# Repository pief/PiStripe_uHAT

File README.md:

# PiStripe uHAT

## Background

Surely I'm not the only one having both a Raspberry Pi and an LED stripe flying around. In my case it was a "dumb", analogue 12V RGB LED stripe, meaning an LED strip without individually addressable LEDs - instead you generate different colors on the entire LED stripe by using pulse width modulation (PWM) on the R, G and B lines.

Interestingly, while there are plenty of tutorials on connecting such an LED stripe to the Raspberry Pi using transistors I wasn't able to find a ready-to-use HAT doing this. There are plenty of HATs driving LEDs directly mounted on the HAT (e.g. [Pimoroni's Ubercorn](https://shop.pimoroni.com/products/ubercorn) and [Unicorn](https://shop.pimoroni.com/products/unicorn-hat) HATs) and
there is [ManiacalLabs' PiPixel HAT](https://www.tindie.com/products/ManiacalLabs/pipixel-raspberry-pi-led-strip-hat/) but that one drives "digital" WS2812-based LED strips, not dumb ones such as mine. Knight of Pi simply [soldered the transistors on Adafruit's ProtoHAT](http://www.knight-of-pi.org/color-mixer-control-a-rgb-led-strip-with-the-raspberry-pi-and-the-n-channel-mosfet-irlb8721/)
but that seemed to me a bit too hackish for permanent use.

The closest existing solution is the [ANAVI Light pHAT](https://www.crowdsupply.com/anavi-technology/light-phat). It is designed for 12V RGB LED strips such as mine, however there were some points I didn't like. For instance, it uses a quite big screw terminal
where I'd prefer a more compact pin header that matches the existing LED strip connector. But most of all, I don't like having to use two power supplies, one with 12V for the LED strip and still one with 5V for the Raspberry Pi. Unfortunately, with the ANAVI pHAT, it was decided to not implement the back powering option, i.e. integrating a switching regulator to convert 12V to 5V and supply these to the Raspberry Pi via the GPIO pins. Instead the PCB space was used for various options for all kinds of sensors,
something I don't really need.

So I thought, inspite of being not literate at electronics enough I'd build something myself and take the best parts and features of existing solutions and combine them into a HAT of my own. After all, that's what open hardware is all about!

And with great success: the PiStripe uHAT has now been built and tested successfully!

## Features

The PiStripe uHAT is a board of the size of the Raspberry Pi Zero, thus a uHAT (not a HAT) as defined by the Raspberry Foundation. It can be attached on any Raspberry Pi with the 40 pin connector, not just the Pi Zero (W).

The uHAT features the following five functions:

- a 12V -> 5V buck converter based on Texas Instruments' [TPS54202](http://www.ti.com/lit/ds/symlink/tps54202.pdf) chip to implement "back powering" the Raspberry Pi via the GPIO pins, doing away with the need to use two power supplies (one 12V for the LED strip, one 5V for the Raspberry Pi).
- a "perfect" reverse current blocking diode schematic as described in the
  [Raspberry Foundation Add-On board / HAT design guide](https://github.com/raspberrypi/hats/blob/master/designguide.md) to prevent damage when accidentally connecting both 5V to the RPi via its MicroUSB connector and supplying power via my HAT does
  not cause damage.
- the actual LED strip driving
- the possibility to connect an external IR receiver such as a TSOP 34838 so you can use [LIRC](http://lirc.org/) to decode the signals sent by the LED strip's original remote control. External because the HAT is mounted on the Raspberry Pi which in turn will probably be hidden away in some corner whereas you will want to place the IR receiver at a place where it can actually "see" the remote control.
- an ID EEPROM so the board qualifies officially as a HAT as described in the [Raspberry Foundation Add-On board / HAT design guide](https://github.com/raspberrypi/hats/blob/master/designguide.md).

## Hardware

The PiStripe uHAT is not a ready-to-buy product. In fact it's not even a product as such. Instead, it's a do-it-yourself project. Consult the **Hardware** directory for the KiCad project files, including a parts list and the PCB ready for etching.

## Software

The PiStripe uHAT's ID EEPROM needs to be programmed once with the binary in the **Software/EEPROM** directory. The **Software** directory additionally contains some examples on how to use the PiStripe uHAT.

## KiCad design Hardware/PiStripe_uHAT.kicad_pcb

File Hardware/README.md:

# PiStripe uHAT

## Hardware

The current v0.7 revision of the PiStripe uHAT has been successfully built and tested with the following remarks nonwithstanding:
- the pullups R9, R11 and R13 are probably unnecessary if the ID EEPROM is changed to use the Raspberry Pi's internal pull-up resistors.
- I used a bit of a too small font size, so if you can't read everything, it's not your eyes...

### GPIOs used

The PiStripe uHAT uses the following GPIO pins:

|          GPIO pins           |    Pin name     |            Usage           | Exclusive |
| :--------------------------: | :-------------: | :------------------------: | :-------: |
|              1, 17           |      +3.3V      |   IR receiver, ID EEPROM   |    No     |
|              2, 4            |       +5V       | Back powering Raspberry Pi |    No     |
| 6, 9, 14, 20, 25, 30, 34, 39 |       GND       |           Ground           |    No     |
|               19             | GPIO10_SPI_MOSI |   LED color 1 (e.g. Red)   |    Yes    |
|               21             | GPIO09_SPI_MISO |  LED color 2 (e.g. Green)  |    Yes    |
|               22             |      GPIO25     |      IR receiver data      |    Yes    |
|               23             | GPIO11_SPI_CLK  |   LED color 3 (e.g. Blue)  |    Yes    |
|               27             |      ID_SD      |     ID EEPROM I2C Data     |    No     |
|               28             |      ID_SC      |     ID EEPROM I2C Clock    |    No     |

### Jumpers

There are two jumpers:

| Jumper |   Name   |                        Function                        |
| :----: | :------: | :----------------------------------------------------: |
|  JP1   | GPIO_PWR | Open: Raspberry Pi is powered over Micro USB connector |
|        | GPIO_PWR | Closed: Enable back powering the Raspberry Pi via GPIO |
|  JP2   |   WR_EN  |                   Open: Normal usage                   |
|        |   WR_EN  |           Closed: ID EEPROM can be programmed          |

Whether you leave JP1 open or closed depends on whether you want to use the "back powering" feature, thus requiring only the LED stripe's +12V power supply, or keep supplying the Raspberry Pi via its Micro USB connector. Even if you accidentally close JP1 and still connect power to the Pi's Micro USB connector, nothing should go wrong thanks to the "perfect" reverse current blocking diode.

JP2 should only be closed once to program the ID EEPROM (no instructions and software for this yet) and stay open afterwards to prevent accidental flashing.

### Design files

The board's schematic and PCB have been designed with [KiCad](http://www.kicad-pcb.org), a really powerful Open Source EDA solution and a worthy alternative to commercial products such as Eagle.

#### Schematic

Here's an image of the schematic:

As you can see, the schematic is clearly divided into different blocks that corrospond to the functions listed above, so comparisons with the original sources for the schematics (see [Credits](#credits)) should be rather easy.

#### PCB

Here are some images of the PCB:

Like the schematic, the PCB has guiding lines printed on top to isolate the different function blocks.

#### Parts list

Please consult the [CSV part list](Hardware/PiStripe_uHAT_Parts.csv) for details.

### Credits

I'm not really inventing something new here but merely combining existing stuff into something new, so I'm standing on the shoulders of giants and try to give appropriate credits here. A big "Thank you" to the following people:

- **Alain Pannetrat** posted the Texas Instruments' [TPS54202](http://www.ti.com/lit/ds/symlink/tps54202.pdf)-based schematic and PCB for [Adding a DC power jack to the Raspberry Pi](https://www.omzlo.com/articles/adding-a-dc-power-jack-to-the-raspberry-pi-v2) on his omzlo.com blog. He did not explicitly specify a license, so I'll assume CC-BY-SA.
- **The Raspberry Foundation** published the circuit for the "perfect" reverse current blocking diode in their [Add-On board / HAT design guide](https://github.com/raspberrypi/hats/blob/master/designguide.md) (see the section "Back Powering the Pi via the GPIO Header" there and the [ZVD circuit schematic](https://github.com/raspberrypi/hats/blob/master/zvd-circuit.png).
- **Leon Anavi** published the schematic and PCB for his [ANAVI Light pHAT](https://www.crowdsupply.com/anavi-technology/light-phat) and his [ANAVI Infrared pHAT](https://www.crowdsupply.com/anavi-technology/infrared-phat) under the [CC-BY-SA 4.0](https://creativecommons.org/licenses/by-sa/4.0/) license. The LED driving circuit, the IR receiver circuit and the basic PCB design such as board dimensions, mounting holes etc. are based on his work. Note that for the IR receiver I use pin 22 (GPI25) instead of pin 12 (GPIO18) to be compatible with the [pHAT DAC](https://de.pinout.xyz/pinout/phat_dac).
- **Mike Lawrence** posted a [RPi_Zero_pHat_Template](https://github.com/mikelawrence/RPi_Zero_pHat_Template) from which I used symbols in ``Connector-ML.lib`` for the schematic. The template is licensed under the [MIT license](https://github.com/mikelawrence/RPi_Zero_pHat_Template/blob/master/LICENSE).
- **Digikey** provides a [KiCAD library](https://github.com/digikey/digikey-kicad-library) from which I used symbols in ``dk_Transistors-FETs-MOSFETs-Single.lib`` for the schematic. The library is licensed under the [CC-BY-SA 4.0](https://github.com/digikey/digikey-kicad-library/blob/master/LICENSE.md) license.
- **L. Bernstone** posted the schematic and design for a [3V3 DC/DC power supply layout using TPS54202](https://github.com/lbernstone/TPS54202/) from which I used symbols in ``tps54202.lib`` for the schematic.
- **Tinkerforge** provides [KiCAD libraries](https://github.com/Tinkerforge/kicad-libraries) from which I used symbols in ``DMMT5401.lib`` for the schematic. They are licensed under the [CERN Open Hardware License v1.1](https://github.com/Tinkerforge/kicad-libraries/blob/master/LICENSE.txt).
- **Philipp "Virtex7" Hörauf** provides a [Philipps Kicad Bauteile collection](https://github.com/Virtex7/PhilippsKicadBauteile/) from which I used the footprint ``SRU1048.kicad_mod`` in the PCB design. Since it didn't provide a 3D model, I modified it to use the one from the following paragraph. Philipp did not explicitly specify a license, so I'll assume CC-BY-SA.
- **ACSE & CADIEEL** provide [CIAA Hardware repository](https://github.com/ciaa/Hardware) from which I used the 3D model ``SRU1048.wrl`` together with the footprint in the previous paragraph. They use [their own license](https://github.com/ciaa/Hardware/blob/master/LICENSE).

### LICENSE

The PiStripe uHAT PCB and its design files are licensed [CC-BY-SA](LICENSE).

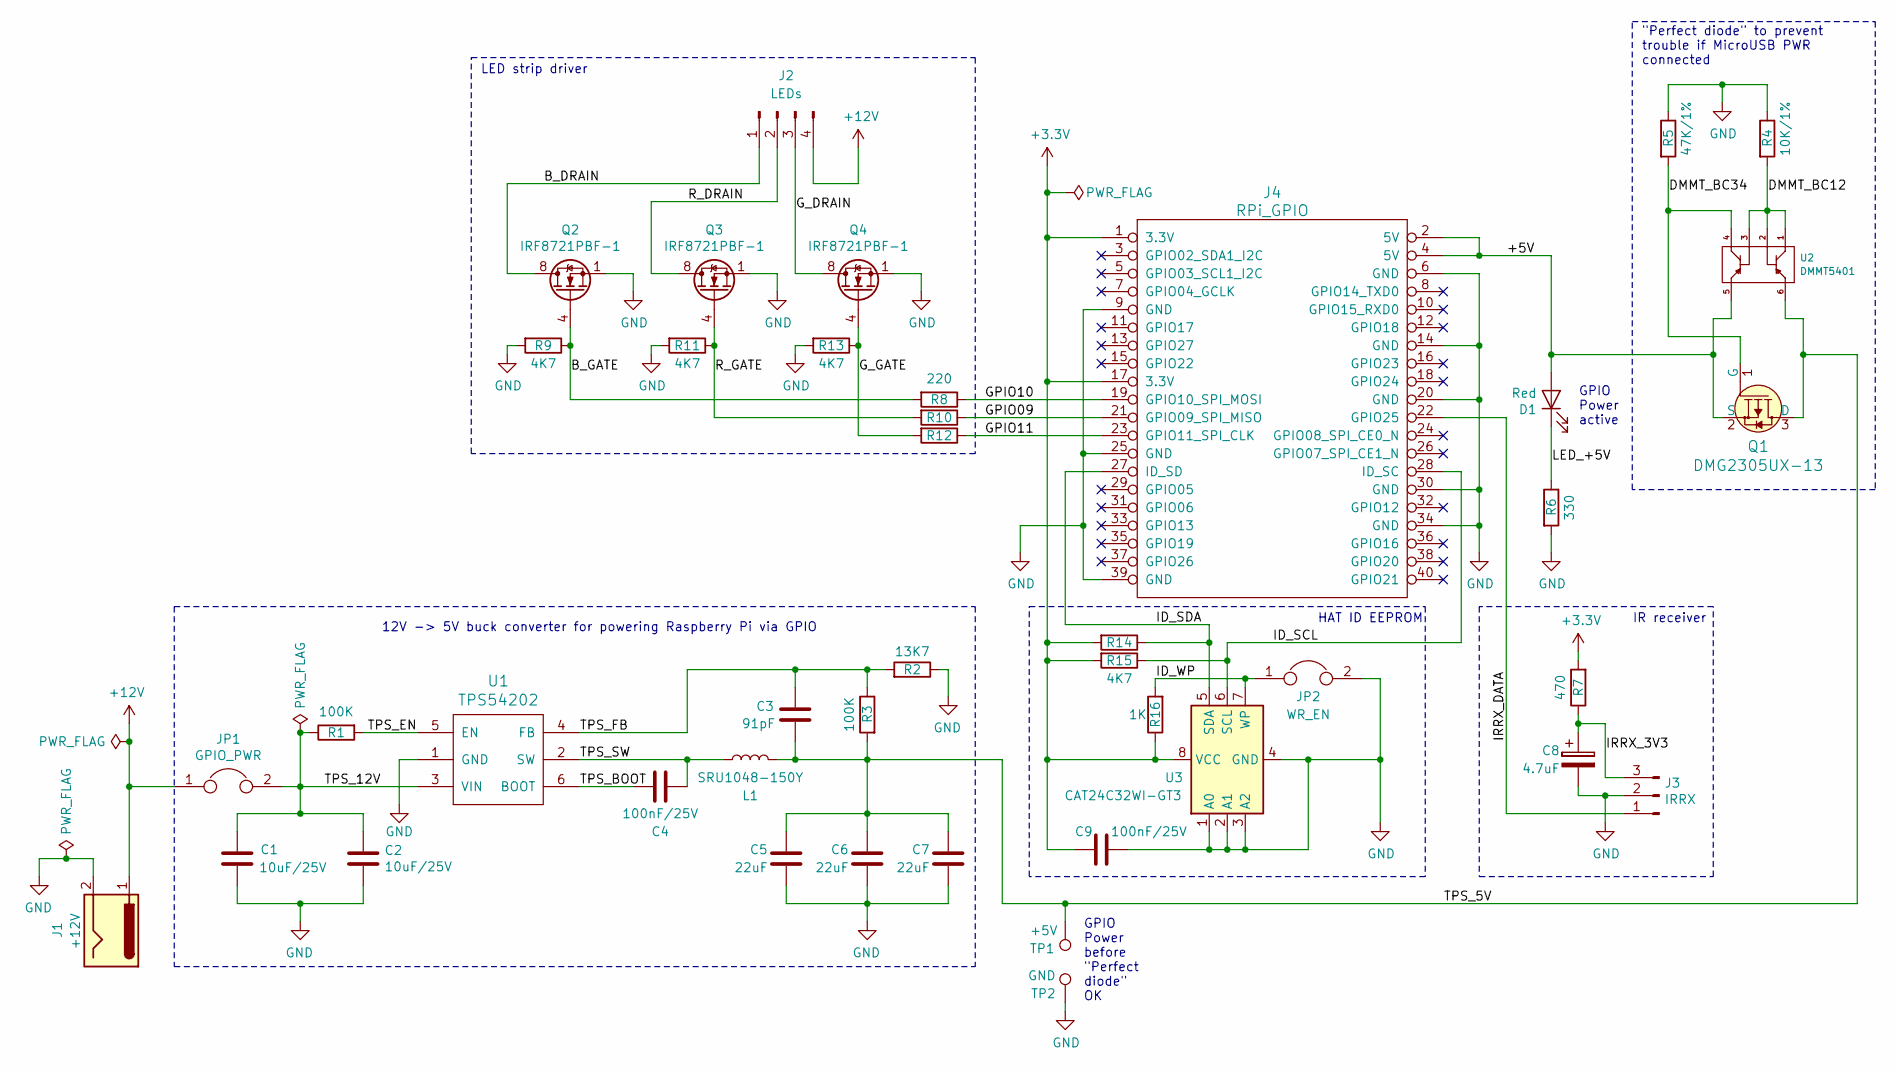
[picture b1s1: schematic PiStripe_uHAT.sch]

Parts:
C1, C2: 10uF/25V; C_0805_2012Metric_Pad1.15x1.40mm_HandSolder
C3: 91pF; C_0805_2012Metric_Pad1.15x1.40mm_HandSolder
C4, C9: 100nF/25V; C_0805_2012Metric_Pad1.15x1.40mm_HandSolder
C5, C6, C7: 22uF; C_0805_2012Metric_Pad1.15x1.40mm_HandSolder
C8: 4.7uF; CP_Elec_4x5.8
D1: Red; D_0805_2012Metric
J1: +12V; BarrelJack_CUI_PJ-063AH_Horizontal
J2: LEDs; PinSocket_1x04_P2.54mm_Horizontal
J3: IRRX; PinHeader_1x03_P2.54mm_Horizontal_Mirrored
J4: RPi_GPIO; PinSocket_2x20_P2.54mm_Vertical
JP1: GPIO_PWR; PinHeader_1x02_P2.54mm_Vertical
JP2: WR_EN; PinHeader_1x02_P1.27mm_Vertical
L1: SRU1048-150Y; SRU1048
Q1: DMG2305UX-13; SOT-23; MPN DMG2305UX-13; Digi-Key_PN DMG2305UX-13DICT-ND
Q2, Q3, Q4: IRF8721PBF-1; SOIC-8_3.9x4.9mm_P1.27mm
R1, R3: 100K; R_0805_2012Metric_Pad1.15x1.40mm_HandSolder
R2: 13K7; R_0805_2012Metric_Pad1.15x1.40mm_HandSolder
R4: 10K/1%; R_0805_2012Metric_Pad1.15x1.40mm_HandSolder
R5: 47K/1%; R_0805_2012Metric_Pad1.15x1.40mm_HandSolder
R6: 330; R_0805_2012Metric_Pad1.15x1.40mm_HandSolder
R7: 470; R_0805_2012Metric_Pad1.15x1.40mm_HandSolder
R8, R10, R12: 220; R_0805_2012Metric_Pad1.15x1.40mm_HandSolder
R9, R11, R13, R14, R15: 4K7; R_0805_2012Metric_Pad1.15x1.40mm_HandSolder
R16: 1K; R_0805_2012Metric_Pad1.15x1.40mm_HandSolder
TP1: +5V; TestPoint_Pad_D1.0mm
TP2: GND; TestPoint_Pad_D1.0mm
U1: TPS54202; SOT-23-6_Handsoldering
U2: DMMT5401; SOT-23-6_Handsoldering
U3: CAT24C32WI-GT3; SOIC-8_3.9x4.9mm_P1.27mm

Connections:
+3V3: C9.2, J4.1 (3.3V), J4.17 (3.3V), R7.2, R14.2, R15.2, R16.1, U3.8 (VCC)
+12V: J1.1, J2.4, JP1.1
/+5V: D1.2 (A), J4.2 (5V), J4.4 (5V), Q1.2 (S), U2.5
/B_DRAIN: J2.1, Q2.5 (D), Q2.6 (D), Q2.7 (D), Q2.8 (D)
/B_GATE: Q2.4 (G), R8.2, R9.1
/DMMT_BC12: R4.2, U2.1, U2.2, U2.3
/DMMT_BC34: Q1.1 (G), R5.2, U2.4
/GPIO09: J4.21 (GPIO09_SPI_MISO), R10.1
/GPIO10: J4.19 (GPIO10_SPI_MOSI), R8.1
/GPIO11: J4.23 (GPIO11_SPI_CLK), R12.1
/G_DRAIN: J2.3, Q4.5 (D), Q4.6 (D), Q4.7 (D), Q4.8 (D)
/G_GATE: Q4.4 (G), R12.2, R13.1
/ID_SCL: J4.28 (ID_SC), R15.1, U3.6 (SCL)
/ID_SDA: J4.27 (ID_SD), R14.1, U3.5 (SDA)
/ID_WP: JP2.1, R16.2, U3.7 (WP)
/IRRX_3V3: C8.1, J3.3, R7.1
/IRRX_DATA: J3.1, J4.22 (GPIO25)
/LED_+5V: D1.1 (K), R6.1
/R_DRAIN: J2.2, Q3.5 (D), Q3.6 (D), Q3.7 (D), Q3.8 (D)
/R_GATE: Q3.4 (G), R10.2, R11.1
/TPS_5V: C3.2, C5.1, C6.1, C7.1, L1.1, Q1.3 (D), R3.2, TP1.1, U2.6
/TPS_12V: C1.1, C2.1, JP1.2, R1.1, U1.3 (VIN)
/TPS_BOOT: C4.1, U1.6 (BOOT)
/TPS_EN: R1.2, U1.5 (EN)
/TPS_FB: C3.1, R2.2, R3.1, U1.4 (FB)
/TPS_SW: C4.2, L1.2, U1.2 (SW)
GND: C1.2, C2.2, C5.2, C6.2, C7.2, C8.2, C9.1, J1.2, J3.2, J4.6 (GND), J4.9 (GND), J4.14 (GND), J4.20 (GND), J4.25 (GND), J4.30 (GND), J4.34 (GND), J4.39 (GND), JP2.2, Q2.1 (S), Q2.2 (S), Q2.3 (S), Q3.1 (S), Q3.2 (S), Q3.3 (S), Q4.1 (S), Q4.2 (S), Q4.3 (S), R2.1, R4.1, R5.1, R6.2, R9.2, R11.2, R13.2, TP2.1, U1.1 (GND), U3.1 (A0), U3.2 (A1), U3.3 (A2), U3.4 (GND)

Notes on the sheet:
"Perfect diode" to prevent trouble if MicroUSB PWR connected
12V -> 5V buck converter for powering Raspberry Pi via GPIO
LED strip driver
IR receiver
HAT ID EEPROM
GPIO Power active
GPIO Power before "Perfect diode" OK

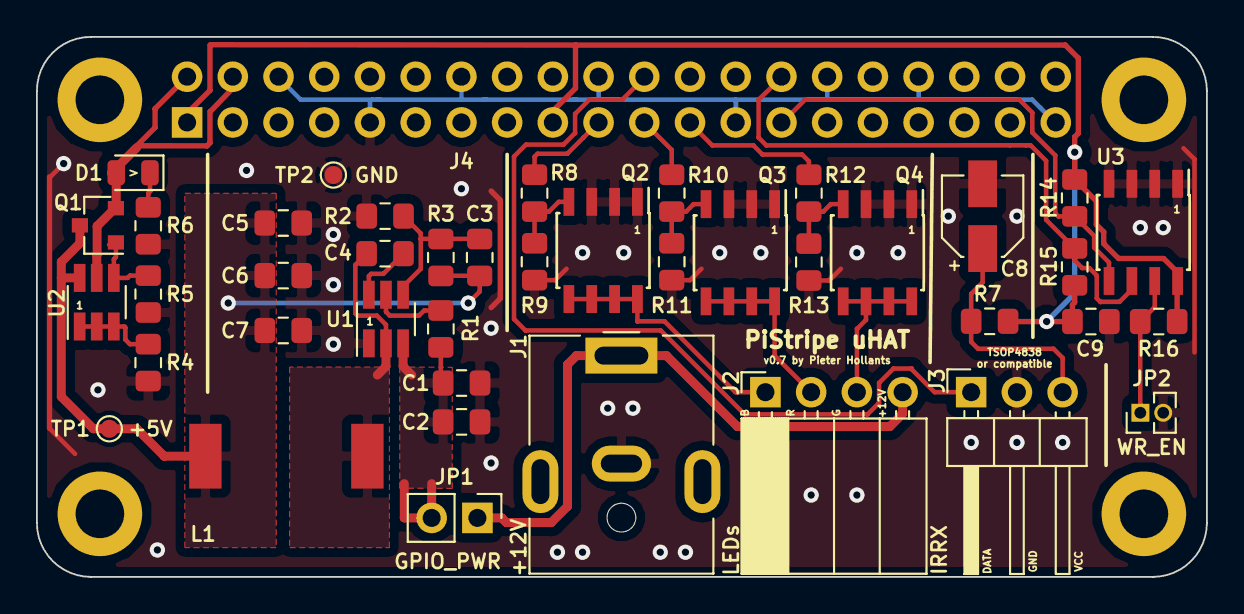
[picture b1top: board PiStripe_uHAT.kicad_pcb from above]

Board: 2 copper layers, 65.0 x 30.0 mm, 46 parts (1 on the bottom side), 27 nets.

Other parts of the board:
REF1, REF2, REF3, REF4: MountingHole_2.7mm_M2.5_DIN965_Pad

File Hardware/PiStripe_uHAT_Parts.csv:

Bezeichner,Gehäuse,Stückzahl,Bezeichnung,Mouser Part No,
"C1,C2",C_0805_2012Metric_Pad1.15x1.40mm_HandSolder,2,10uF/25V,81-GRM21BC81E106KE5L,
C3,C_0805_2012Metric_Pad1.15x1.40mm_HandSolder,1,91pF,581-08055A910JAT2A,
"C4,C9",C_0805_2012Metric_Pad1.15x1.40mm_HandSolder,2,100nF/25V,581-08053C104J,
"C5,C6,C7",C_0805_2012Metric_Pad1.15x1.40mm_HandSolder,3,22uF,81-GRM21BD71A226ME4L,
C8,CP_Elec_4x5.8,1,4.7uF,667-EEE-HC1V4R7R,
D1,D_0805_2012Metric,1,Red,645-599-0110-007F,
J1,BarrelJack_CUI_PJ-063AH_Horizontal,1,+12V,490-PJ-063AH,
J2,PinSocket_1x04_P2.54mm_Horizontal,1,LEDs,437-8018700420001101,
J3,PinHeader_1x03_P2.54mm_Horizontal_Mirrored,1,IRRX,200-HMTSW1037TS110RA ,
J4,PinSocket_2x20_P2.54mm_Vertical,1,RPi_GPIO,485-2223 ,
JP1,PinHeader_1x02_P2.54mm_Vertical,1,GPIO_PWR,855-M7583-05,855-M20-9770242
JP2,PinHeader_1x02_P1.27mm_Vertical,1,WR_EN,855-M50-1920005,855-M50-3530242
L1,SRU1048,1,SRU1048-150Y,652-SRU1048-150Y,
Q1,SOT-23,1,DMG2305UX-13,621-DMG2305UX-7,
"Q2,Q3,Q4",SOIC-8_3.9x4.9mm_P1.27mm,3,IRF8721PBF-1,942-IRF8721TRPBF,
"R1,R3",R_0805_2012Metric_Pad1.15x1.40mm_HandSolder,2,100K,754-RR1220P-104D,
"R14,R15,R9,R11,R13",R_0805_2012Metric_Pad1.15x1.40mm_HandSolder,5,4K7,754-RR1220P-472D,
R16,R_0805_2012Metric_Pad1.15x1.40mm_HandSolder,1,1K,754-RR1220P-102D,
R2,R_0805_2012Metric_Pad1.15x1.40mm_HandSolder,1,13K7,754-RR1220P-1372D-M,
R4,R_0805_2012Metric_Pad1.15x1.40mm_HandSolder,1,10K/1%,754-RR1220P-103D,
R5,R_0805_2012Metric_Pad1.15x1.40mm_HandSolder,1,47K/1%,754-RR1220P-473D,
R6,R_0805_2012Metric_Pad1.15x1.40mm_HandSolder,1,330,754-RR1220P-331D,
R7,R_0805_2012Metric_Pad1.15x1.40mm_HandSolder,1,470,754-RR1220P-471D,
"R8,R10,R12",R_0805_2012Metric_Pad1.15x1.40mm_HandSolder,3,220,754-RR1220P-221D,
U1,SOT-23-6_Handsoldering,1,TPS54202,595-TPS54202DDCR,
U2,SOT-23-6_Handsoldering,1,DMMT5401,621-DMMT5401-7-F,
U3,SOIC-8_3.9x4.9mm_P1.27mm,1,CAT24C32WI-GT3,698-CAT24C32WI-GT3,

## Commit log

2018-12-20 Add first version of toplevel README.md
2018-12-21 README.md: Fix links
2018-12-21 Restructure, add first credits
2018-12-21 More updates
2018-12-21 Remove superfluous README.md in hardware folder
2018-12-21 Replace LICENSE.md in Hardware folder with LICENSE
2018-12-21 Add images of schematic and PCB
2018-12-21 Add images to README
2018-12-21 Moar updates
2018-12-21 Add used GPIO pins to README.md
2018-12-21 README.md: Link to Credits section
2018-12-21 README.md: Add section on Jumpers
2018-12-21 Rename image to PiStripe_uHAT-PCB-Top-NoParts.png
2018-12-21 PCB: Add one more guide line, move C5-C7 a bit
2018-12-21 README.md: Fix path
2018-12-23 v0.2: Small purely cosmetical update to the PCB
2018-12-23 v0.3: Additional Vias on GND plane near TPS54202, C9 routing optimized
2018-12-23 Fix pictures
2018-12-23 Add .gitignore to ignore *bak files
2018-12-23 v0.4: Change GPIO for IRRX from Pin 12 (GPIO18) to 22 (GPIO25)
    Pin 12/GPIO18 is used by the phatDAC HAT which I want to combine with my
    PiStripe uHAT.
2018-12-23 README.md: Update IRRX pin for v0.4
2018-12-23 README.md: Explain GPIO difference to ANAVI Infrared pHAT
2018-12-24 Turn GND arrows down in schematic
2018-12-25 Add LIRC configuration file for and photo of my LED stripe remote
2018-12-25 Schematic: Tidy up IR receiver section
2018-12-25 Board v0.5: Tidy right half of PCB
    - Move Q2/Q3/Q4 more to the left
    - Use generated space to move U3, R11, R12, R13 and C9 up right, placing
    JP2 below U3, making it visually easier to find
    - Move C8 next to R10, above J3
    - Connect to J1 separately from both sides to ensure better voltage flow
    - Add pin description labels to J2 and J3 (note J2 R/G/B assignment may
2018-12-26 Clean up PCB wires
2018-12-26 Updated parts list
2018-12-26 Add parts list to README
2018-12-26 Schematic: Correct label text orientation
2018-12-26 Use 25V instead of 50V for C1, C2, C4
    Should be totally sufficient and is available in 0805 form factor.
2019-01-02 v0.6: Pulldowns for GPIO 09-11, reroute IRRX DATA, correct footprints etc.
    - Added pulldown resistors on GPIO 09-11, the gate lines of the IRF8721PBFs
    to ensure an undefined state at powerup doesn't cause the MOSFETs to
    operate and make the LEDs flicker.
    - Named nets in schematic for easier tracing in the PCB design.
    - Rerouted IRRX DATA line on top side to avoid long GND-dividing trace on
    bottom side.
2019-01-13 v0.7: Correct connections and footprints for J2 and J3
    - Corrected J2 connections from R/G/B/+12V to B/R/G/+12V layout
    because that's what most LED strips actually use connector-wise.
    - Flipped J3 connections, Pin 1/DATA is now left, so that you can
    solder in a TSOP4838 directly if you want to.
    - Corrected footprints for J2 and J3 to 2.54mm pitch.
    - This required moving J1 and the entire voltage regulator
2019-01-13 Fix typo in README.md
2019-02-21 Add sources and Makefile for building the contents for the ID EEPROM
2019-02-21 Add initial version of binary for ID EEPROM
2019-02-21 EEPROM Makefile: Do not remove PiStripe_uHAT.eep on clean
2019-02-21 Remove LIRC config in favor of gpio-ir decoding RC codes
2019-02-21 Add Python example to test for remote control's scancodes
2019-02-21 Add README.md for Software directory
2019-02-21 Fix boldface in Software README.md
2019-02-21 Software README.md: experiment with links
2019-02-21 Software README.md: OK, forget about links
2019-02-21 EEPROM README.md: Update typography
2019-02-21 Move hardware-specific info into Hardware/README.md & add v0.7 success
2019-02-21 Fix paths in Hardware/README.md
2019-02-21 Fix link to license in Hardware/README.md
2019-02-21 Update README.md to clarify it's not a product
2019-02-21 Make test_scancodes.py executable
